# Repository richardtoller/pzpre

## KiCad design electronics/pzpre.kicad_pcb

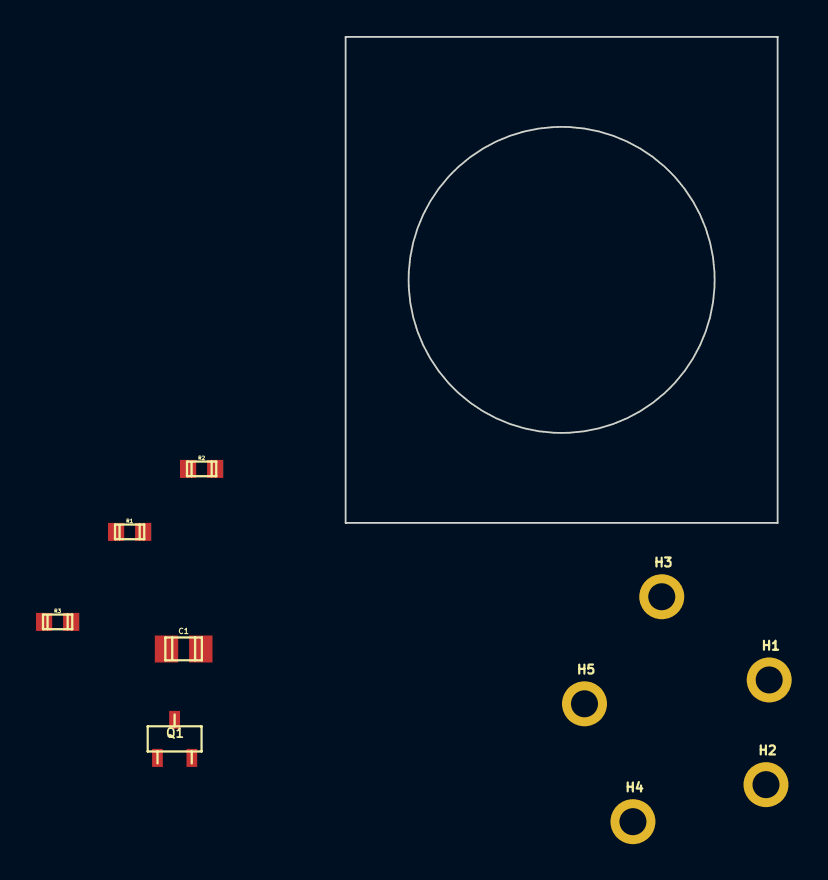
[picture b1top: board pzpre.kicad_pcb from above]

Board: 2 copper layers, 24.0 x 27.0 mm, 10 parts (0 on the bottom side), 6 nets, no tracks yet.

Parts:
C1: C; c_0805
H1, H2, H3, H4, H5: HOLE; PLATED_HOLE_1_5MM
Q1: 2SK3666; sot23
R1, R2, R3: R; r_0603

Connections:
unnamed: C1.1, H3.1
unnamed: C1.2, Q1.2, R2.2
unnamed: H1.1, R2.1
unnamed: H2.1, H4.1, R1.2, R3.2
unnamed: H5.1, Q1.3, R1.1
unnamed: Q1.1, R3.1
